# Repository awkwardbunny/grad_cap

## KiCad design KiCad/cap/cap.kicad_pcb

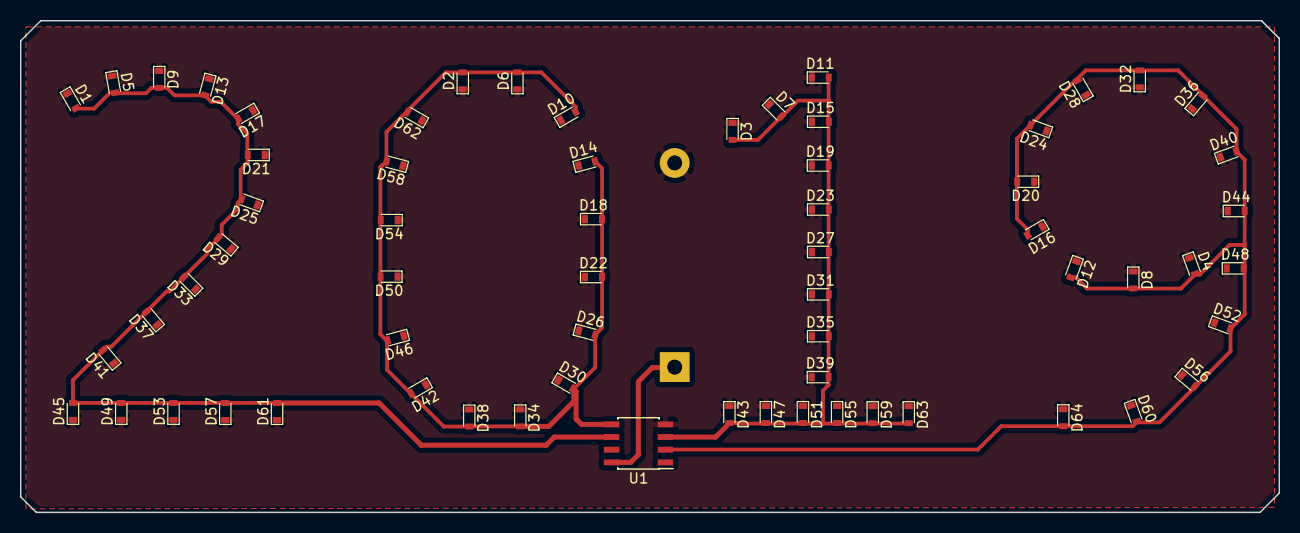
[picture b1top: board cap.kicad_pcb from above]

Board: 2 copper layers, 126.3 x 49.3 mm, 66 parts (1 on the bottom side), 6 nets.

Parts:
BT1: Battery_Cell; Keystone_103_1x20mm-CoinCell
D1, D2, D3, D4, D5, D6, D7, D8, D9, D10, D11, D12, D13, D14, D15, D16, D17, D18, D19, D20, D21, D22, D23, D24, D25, D26, D27, D28, D29, D30, D31, D32, D33, D34, D35, D36, D37, D38, D39, D40, D41, D42, D43, D44, D45, D46, D47, D48, D49, D50, D51, D52, D53, D54, D55, D56, D57, D58, D59, D60, D61, D62, D63, D64: LED; D_0603
U1: ATtiny85-20SU; SOIC-8_3.9x4.9mm_Pitch1.27mm

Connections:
GND: BT1.2, D1.1, D2.1, D3.1, D4.1, D5.1, D6.1, D7.1, D8.1, D9.1, D10.1, D11.1, D12.1, D13.1, D14.1, D15.1, D16.1, D17.1, D18.1, D19.1, D20.1, D21.1, D22.1, D23.1, D24.1, D25.1, D26.1, D27.1, D28.1, D29.1, D30.1, D31.1, D32.1, D33.1, D34.1, D35.1, D36.1, D37.1, D38.1, D39.1, D40.1, D41.1, D42.1, D43.1, D44.1, D45.1, D46.1, D47.1, D48.1, D49.1, D50.1, D51.1, D52.1, D53.1, D54.1, D55.1, D56.1, D57.1, D58.1, D59.1, D60.1, D61.1, D62.1, D63.1, D64.1, U1.4
unnamed: BT1.1, U1.8
unnamed: D1.2, D5.2, D9.2, D13.2, D17.2, D21.2, D25.2, D29.2, D33.2, D37.2, D41.2, D45.2, D49.2, D53.2, D57.2, D61.2, U1.6
unnamed: D2.2, D6.2, D10.2, D14.2, D18.2, D22.2, D26.2, D30.2, D34.2, D38.2, D42.2, D46.2, D50.2, D54.2, D58.2, D62.2, U1.5
unnamed: D3.2, D7.2, D11.2, D15.2, D19.2, D23.2, D27.2, D31.2, D35.2, D39.2, D43.2, D47.2, D51.2, D55.2, D59.2, D63.2, U1.3
unnamed: D4.2, D8.2, D12.2, D16.2, D20.2, D24.2, D28.2, D32.2, D36.2, D40.2, D44.2, D48.2, D52.2, D56.2, D60.2, D64.2, U1.2

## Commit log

2019-05-15 Initial Design
    I forgot the programming header...
